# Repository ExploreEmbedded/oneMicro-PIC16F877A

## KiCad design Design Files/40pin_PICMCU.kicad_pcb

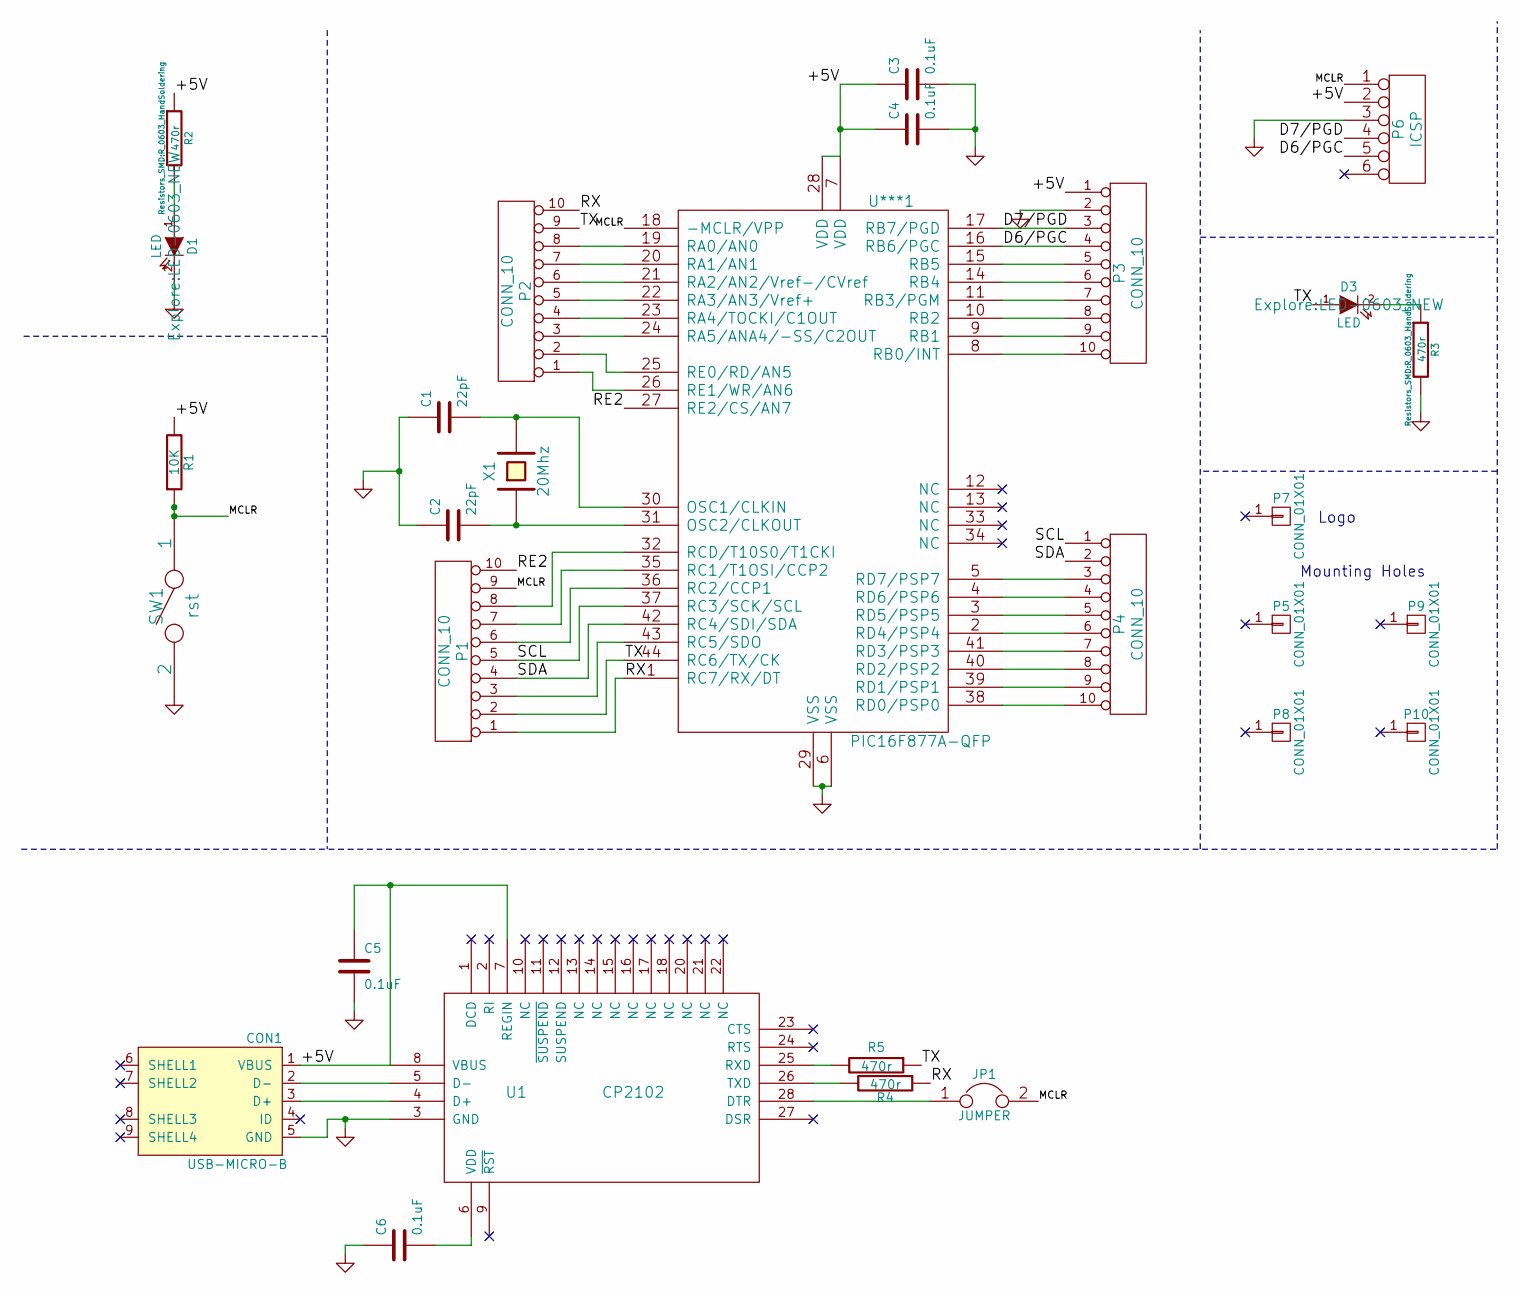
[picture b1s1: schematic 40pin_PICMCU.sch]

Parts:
C1, C2: 22pF; C_0603_HandSoldering
C3, C4, C5, C6: 0.1uF; C_0603_HandSoldering
CON1: USB-MICRO-B; USB_Micro-B_SMD_NEW_1
D1, D3: LED; LED-0603_NEW
JP1: JUMPER; Pin_Header_Straight_1x02_Pitch2.54mm
P1, P2, P3, P4: CONN_10; Pin_Header_Straight_1x10_Pitch2.54mm
P5, P8, P9, P10: CONN_01X01; 1pin
P6: ICSP; Pin_Header_Straight_1x06_Pitch2.54mm
P7: CONN_01X01; Logo_8
R1: 10K; R_0603_HandSoldering
R2, R3, R4, R5: 470r; R_0603_HandSoldering
SW1: rst; SW_PUSH_SMALL_2pin_3D_xl_v1
U1: CP2102; cp2102_xl2
U***1: PIC16F877A-QFP; LQFP-44_10x10mm_Pitch0.8mm
X1: 20Mhz; Crystal_HC18-U_Vertical

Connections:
/+5V: C3.1, C4.1, C5.1, CON1.1 (VBUS), P3.1, P6.2, R1.2, R2.1, U1.7 (REGIN), U1.8 (VBUS), U***1.7 (VDD), U***1.28 (VDD)
/D6/PGC: P3.4, P6.5, U***1.16 (RB6/PGC)
/D7/PGD: P3.3, P6.4, U***1.17 (RB7/PGD)
/MCLR: JP1.2, P1.9, P6.1, R1.1, SW1.1, U***1.18 (-MCLR/VPP)
/RE2: P1.10, U***1.27 (RE2/CS/AN7)
/RX: P1.1, P2.10, R4.1, U***1.1 (RC7/RX/DT)
/SCL: P1.5, P4.1, U***1.37 (RC3/SCK/SCL)
/SDA: P1.4, P4.2, U***1.42 (RC4/SDI/SDA)
/TX: D3.1 (A), P1.2, P2.9, R5.1, U***1.44 (RC6/TX/CK)
GND: C1.1, C2.1, C3.2, C4.2, C5.2, C6.1, CON1.5 (GND), D1.2 (K), P3.2, P6.3, R3.2, SW1.2, U1.3 (GND), U***1.6 (VSS), U***1.29 (VSS)
unnamed: C1.2, U***1.30 (OSC1/CLKIN), X1.2
unnamed: C2.2, U***1.31 (OSC2/CLKOUT), X1.1
unnamed: C6.2, U1.6 (VDD)
unnamed: CON1.2 (D-), U1.5 (D-)
unnamed: CON1.3 (D+), U1.4 (D+)
unnamed: D1.1 (A), R2.2
unnamed: D3.2 (K), R3.1
unnamed: JP1.1, U1.28 (DTR)
unnamed: P1.3, U***1.43 (RC5/SDO)
unnamed: P1.6, U***1.36 (RC2/CCP1)
unnamed: P1.7, U***1.35 (RC1/T1OSI/CCP2)
unnamed: P1.8, U***1.32 (RCD/T10S0/T1CKI)
unnamed: P2.1, U***1.26 (RE1/WR/AN6)
unnamed: P2.2, U***1.25 (RE0/RD/AN5)
unnamed: P2.3, U***1.24 (RA5/ANA4/-SS/C2OUT)
unnamed: P2.4, U***1.23 (RA4/TOCKI/C1OUT)
unnamed: P2.5, U***1.22 (RA3/AN3/Vref+)
unnamed: P2.6, U***1.21 (RA2/AN2/Vref-/CVref)
unnamed: P2.7, U***1.20 (RA1/AN1)
unnamed: P2.8, U***1.19 (RA0/AN0)
unnamed: P3.5, U***1.15 (RB5)
unnamed: P3.6, U***1.14 (RB4)
unnamed: P3.7, U***1.11 (RB3/PGM)
unnamed: P3.8, U***1.10 (RB2)
unnamed: P3.9, U***1.9 (RB1)
unnamed: P3.10, U***1.8 (RB0/INT)
unnamed: P4.3, U***1.5 (RD7/PSP7)
unnamed: P4.4, U***1.4 (RD6/PSP6)
unnamed: P4.5, U***1.3 (RD5/PSP5)
unnamed: P4.6, U***1.2 (RD4/PSP4)
unnamed: P4.7, U***1.41 (RD3/PSP3)
unnamed: P4.8, U***1.40 (RD2/PSP2)
unnamed: P4.9, U***1.39 (RD1/PSP1)
unnamed: P4.10, U***1.38 (RD0/PSP0)
unnamed: R4.2, U1.26 (TXD)
unnamed: R5.2, U1.25 (RXD)

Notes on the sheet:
Logo
Mounting Holes

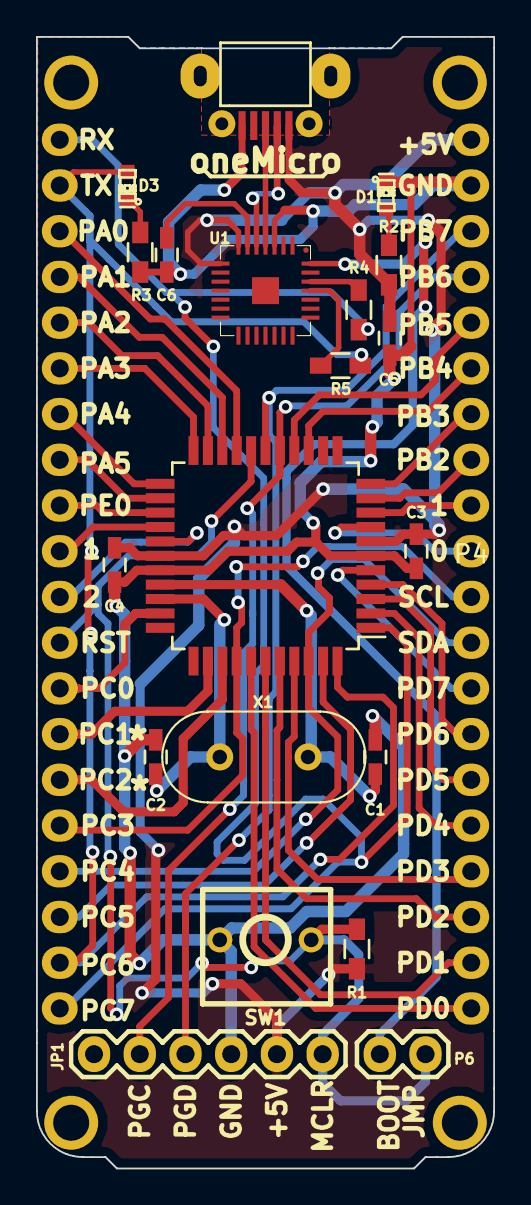
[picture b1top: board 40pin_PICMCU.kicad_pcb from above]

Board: 2 copper layers, 25.4 x 62.9 mm, 29 parts (1 on the bottom side), 46 nets.

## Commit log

2016-07-28 Added design Files
2016-07-29 Updated Designs
2016-07-30 proposed a little change in layout
2016-07-30 Routing
2016-09-08 Design file updated
2017-03-17 Changes Done
2017-07-11 BOM generated
2017-08-11 Added Reset connectin
2017-08-11 Revised gerber file generated for v1.0
